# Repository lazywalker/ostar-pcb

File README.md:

# ostar-pcb
PCB files for Ostar system board

* Same sizes and mounting holes of Raspberry Pi Zero W
* Works with [Ostar](https://github.com/lazywalker/mmdvm-openwrt)

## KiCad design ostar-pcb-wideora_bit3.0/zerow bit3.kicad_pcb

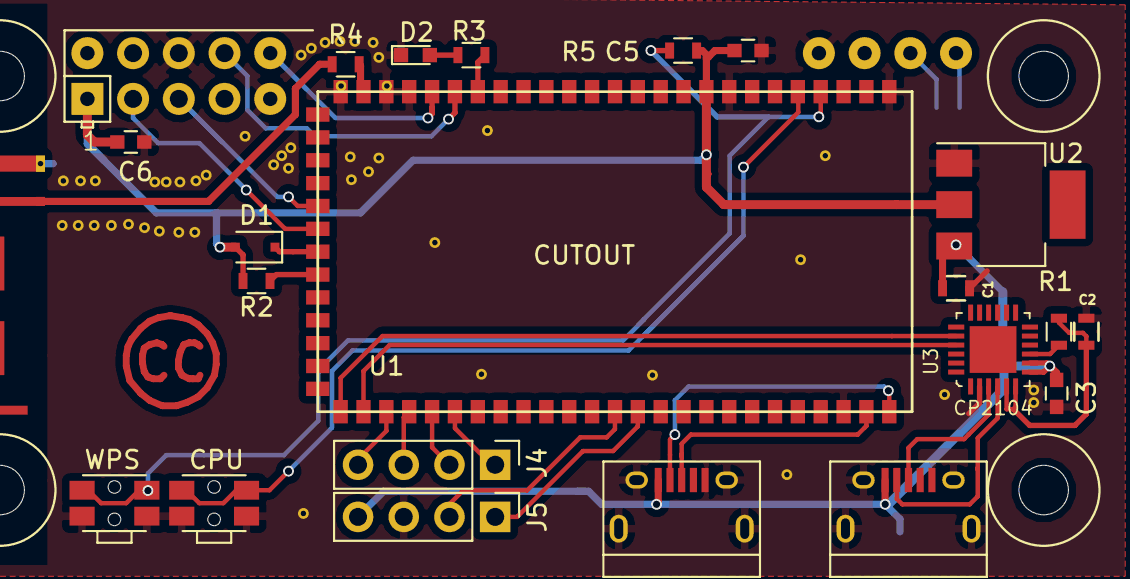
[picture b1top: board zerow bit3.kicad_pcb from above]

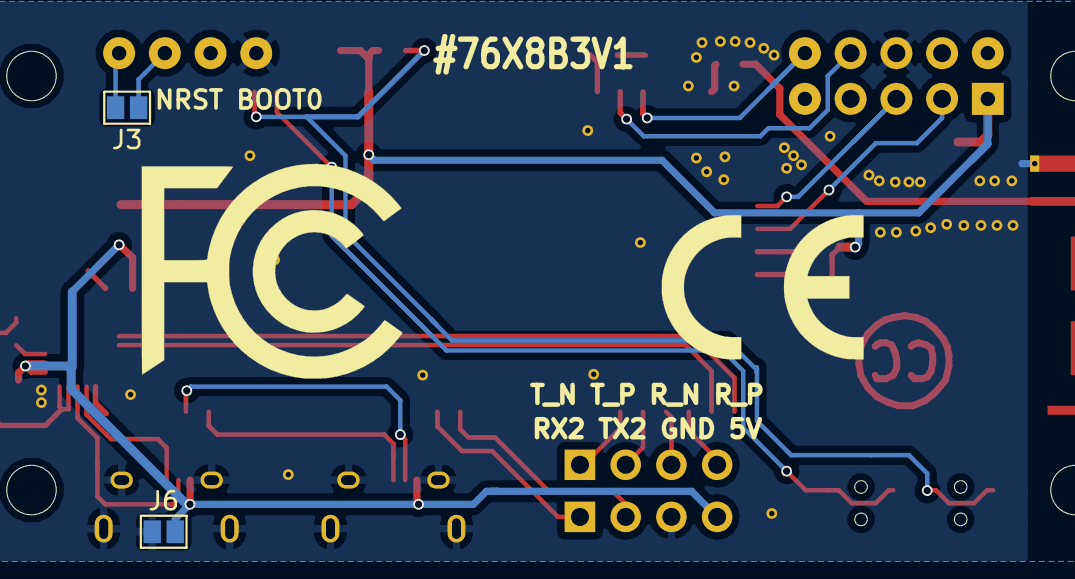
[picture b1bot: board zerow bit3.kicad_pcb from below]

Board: 2 copper layers, 25 parts (2 on the bottom side), 31 nets.

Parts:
AE1: Antenna_Shield; Texas_SWRA117D_2.4GHz_Left1
C1, C2: 2.2uF; R_0603
C3, C5, C6: 2.2uF; C_0603
D1: S1; D_SOD-323F
D2: LED; LED_0603
J1, J2: USB_OTG; USB_Micro-B
J3: Conn_01x02; GS2
J4: RJ45; Pin_Header_Straight_1x04_Pitch2.54mm
J5: Conn_01x04; Pin_Header_Straight_1x04_Pitch2.54mm
J6: PWR; GS2
PI1: RPI-ZERO; RPI-Zero-BIT3
R1, R5: 5.1K; R_0603
R2, R3: 1K; R_0603
R4: 0R; R_0603
SW1: WPS; SW_SPST_EVQP7C
SW2: CPU; SW_SPST_EVQP7C
U1: BIT3; BIT3_wideora
U2: LT1084-3.3; SOT-223
U3: CP2104; qfn24

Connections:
+3V3: C5.1, C6.1, D1.2, PI1.1, R2.2, R5.2, U1.34, U2.2
+5V: C1.2, C3.1, J1.1, J2.1, J5.4, J6.1, U2.3, U3.7, U3.8
GND: AE1.2, C1.1, C2.1, C3.2, C5.2, C6.2, D2.1, J1.5, J1.6, J2.5, J2.6, J5.3, J6.2, PI1.6, PI1.9, PI1.34, SW1.2, SW2.2, U1.23, U1.26, U1.33, U1.47, U1.48, U1.50, U2.1, U3.2
unnamed: AE1.1, R4.1
unnamed: C2.2, R1.2, U3.5, U3.6
unnamed: D1.1, U1.57
unnamed: D2.2, R3.1
unnamed: J1.2, U1.25
unnamed: J1.3, U1.24
unnamed: J2.2, U3.4
unnamed: J2.3, U3.3
unnamed: J3.1, PI1.38
unnamed: J3.2, PI1.40
unnamed: J4.1, U1.6
unnamed: J4.2, U1.5
unnamed: J4.3, U1.4
unnamed: J4.4, U1.3
unnamed: J5.1, U1.14
unnamed: J5.2, U1.13
unnamed: PI1.3, U1.56
unnamed: PI1.5, U1.55
unnamed: PI1.8, U1.45
unnamed: PI1.10, U1.46
unnamed: R1.1, U3.9
unnamed: R2.1, U1.58
unnamed: R3.2, U1.44
unnamed: R4.2, U1.49
unnamed: R5.1, SW1.1, U1.29
unnamed: SW2.1, U1.30
unnamed: U1.1, U3.20
unnamed: U1.2, U3.21

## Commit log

2021-10-25 typo
2021-10-25 fix image url
